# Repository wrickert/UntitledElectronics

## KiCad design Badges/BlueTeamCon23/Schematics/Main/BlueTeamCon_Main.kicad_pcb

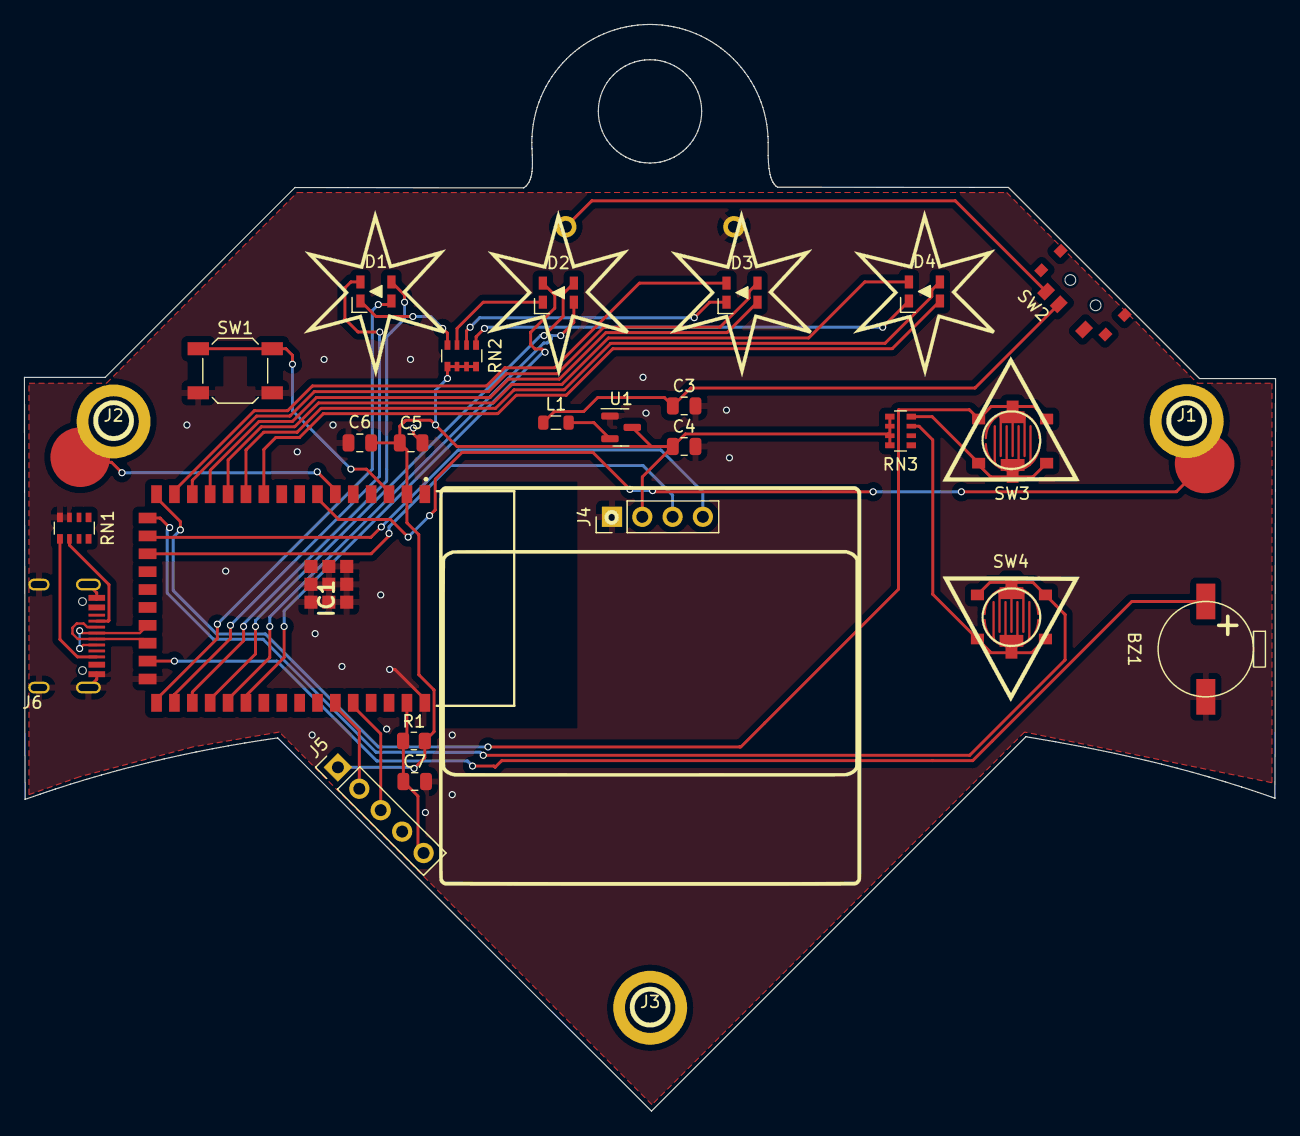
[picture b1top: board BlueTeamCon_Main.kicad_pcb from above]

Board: 2 copper layers, 104.9 x 91.1 mm, 30 parts (1 on the bottom side), 39 nets.

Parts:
BT1: Battery; AA_TH
BZ1: Buzzer; FUET-9032-Buzzer
C3: 10uF; C_0805_2012Metric
C4, C5: 22uF; C_0805_2012Metric
C6, C7: 100nF; C_0805_2012Metric
D1, D2, D3, D4: LED_RGBA; XL-3227RGB_LED
IC1: ESP32-S2-WROOM-I_M22S2H3200US3Q0_; ESP32S2WROOMIM22S2H3200US3Q0
J1, J2, J3: Conn_01x01; Threaded_Standoffs
J4: Display; PinHeader_1x04_P2.54mm_Vertical
J5: Conn_01x05; PinHeader_1x05_P2.54mm_Vertical
J6: USB_C_Plug_USB2.0; USB_C_Receptical-Jing
J7, J8: Cap Sense; CapSense
L1: 10uH; L_0805_2012Metric
R1: 1k; R_0805_2012Metric
RN1: 5.1k; R_Array_Convex_4x0603
RN2, RN3: R_Pack04; R_Array_Convex_4x0603
SW1: Boot; SW_SPST_SKQG_WithoutStem
SW2: SW_SPDT; SK-3296S_switch
SW3: A; BZCN-TSC005A_Button
SW4: B; BZCN-TSC005A_Button
U1: SOT-23

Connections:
+5V: J6.A4 (VBUS), J6.A9 (VBUS), J6.B4 (VBUS), J6.B9 (VBUS)
/D+: IC1.23 (IO20), J6.A6 (D+), J6.B6 (D+)
/D-: IC1.24 (IO21), J6.A7 (D-), J6.B7 (D-)
A_Btn: IC1.16 (IO13), SW3.1
B: IC1.17 (IO14), SW4.1
B1: D1.4 (BK), IC1.27 (IO33)
B2: D2.4 (BK), IC1.31 (IO37)
B3: D3.4 (BK), IC1.13 (IO10)
B4: D4.4 (BK), IC1.10 (IO7)
Boot: IC1.3 (IO0), SW1.1
Buzzer: BZ1.1 (-), IC1.25 (IO26)
G1: D1.2 (GK), IC1.29 (IO35)
G2: D2.2 (GK), IC1.30 (IO36)
G3: D3.2 (GK), IC1.14 (IO11)
G4: D4.2 (GK), IC1.11 (IO8)
unnamed: D1.3 (A), RN2.4 (R4.1)
unnamed: D2.3 (A), RN2.3 (R3.1)
unnamed: D3.3 (A), RN2.2 (R2.1)
unnamed: D4.3 (A), RN2.1 (R1.1)
unnamed: IC1.6 (IO3), J7.1
unnamed: IC1.7 (IO4), J8.1
unnamed: J6.A5 (CC1), RN1.6 (R3.2)
unnamed: J6.B5 (CC2), RN1.5 (R4.2)
unnamed: RN3.3 (R3.1), SW4.2
unnamed: RN3.4 (R4.1), SW3.2
unnamed: L1.2, U1.2 (LX)
PwrTest: C3.1, L1.1, SW2.2 (B)
R1: D1.1 (RK), IC1.28 (IO34)
R2: D2.1 (RK), IC1.32 (IO38)
R3: D3.1 (RK), IC1.15 (IO12)
R4: D4.1 (RK), IC1.12 (IO9)
RX: IC1.38 (RXD0), J5.3
Reset: C7.1, IC1.41 (EN), J5.5, R1.1
SCK: IC1.19 (IO16), J4.3
SDA: IC1.18 (IO15), J4.4
TX: IC1.37 (TXD0), J5.2
VCC: C4.1, C5.1, C6.1, IC1.2 (3V3), J4.2, J5.1, R1.2, RN2.5 (R4.2), RN2.6 (R3.2), RN2.7 (R2.2), RN2.8 (R1.2), RN3.5 (R4.2), RN3.6 (R3.2), RN3.7 (R2.2), RN3.8 (R1.2), U1.3 (VOUT)
VDD: BT1.1 (+), SW2.1 (A)
VSS: BT1.2 (-), BZ1.2 (+), C3.2, C4.2, C5.2, C6.2, C7.2, IC1.1 (GND_1), IC1.26 (GND_2), IC1.42 (GND_3), IC1.43 (GND_4), IC1.44 (GND_5), IC1.45 (GND_6), IC1.46 (GND_7), IC1.47 (GND_8), IC1.48 (GND_9), IC1.49 (GND_10), IC1.50 (GND_11), IC1.51 (GND_12), J4.1, J5.4, J6.A1 (GND), J6.A12 (GND), J6.B1 (GND), J6.B12 (GND), J6.S1 (SHIELD), RN1.3 (R3.1), RN1.4 (R4.1), SW1.2, U1.1 (VSS)

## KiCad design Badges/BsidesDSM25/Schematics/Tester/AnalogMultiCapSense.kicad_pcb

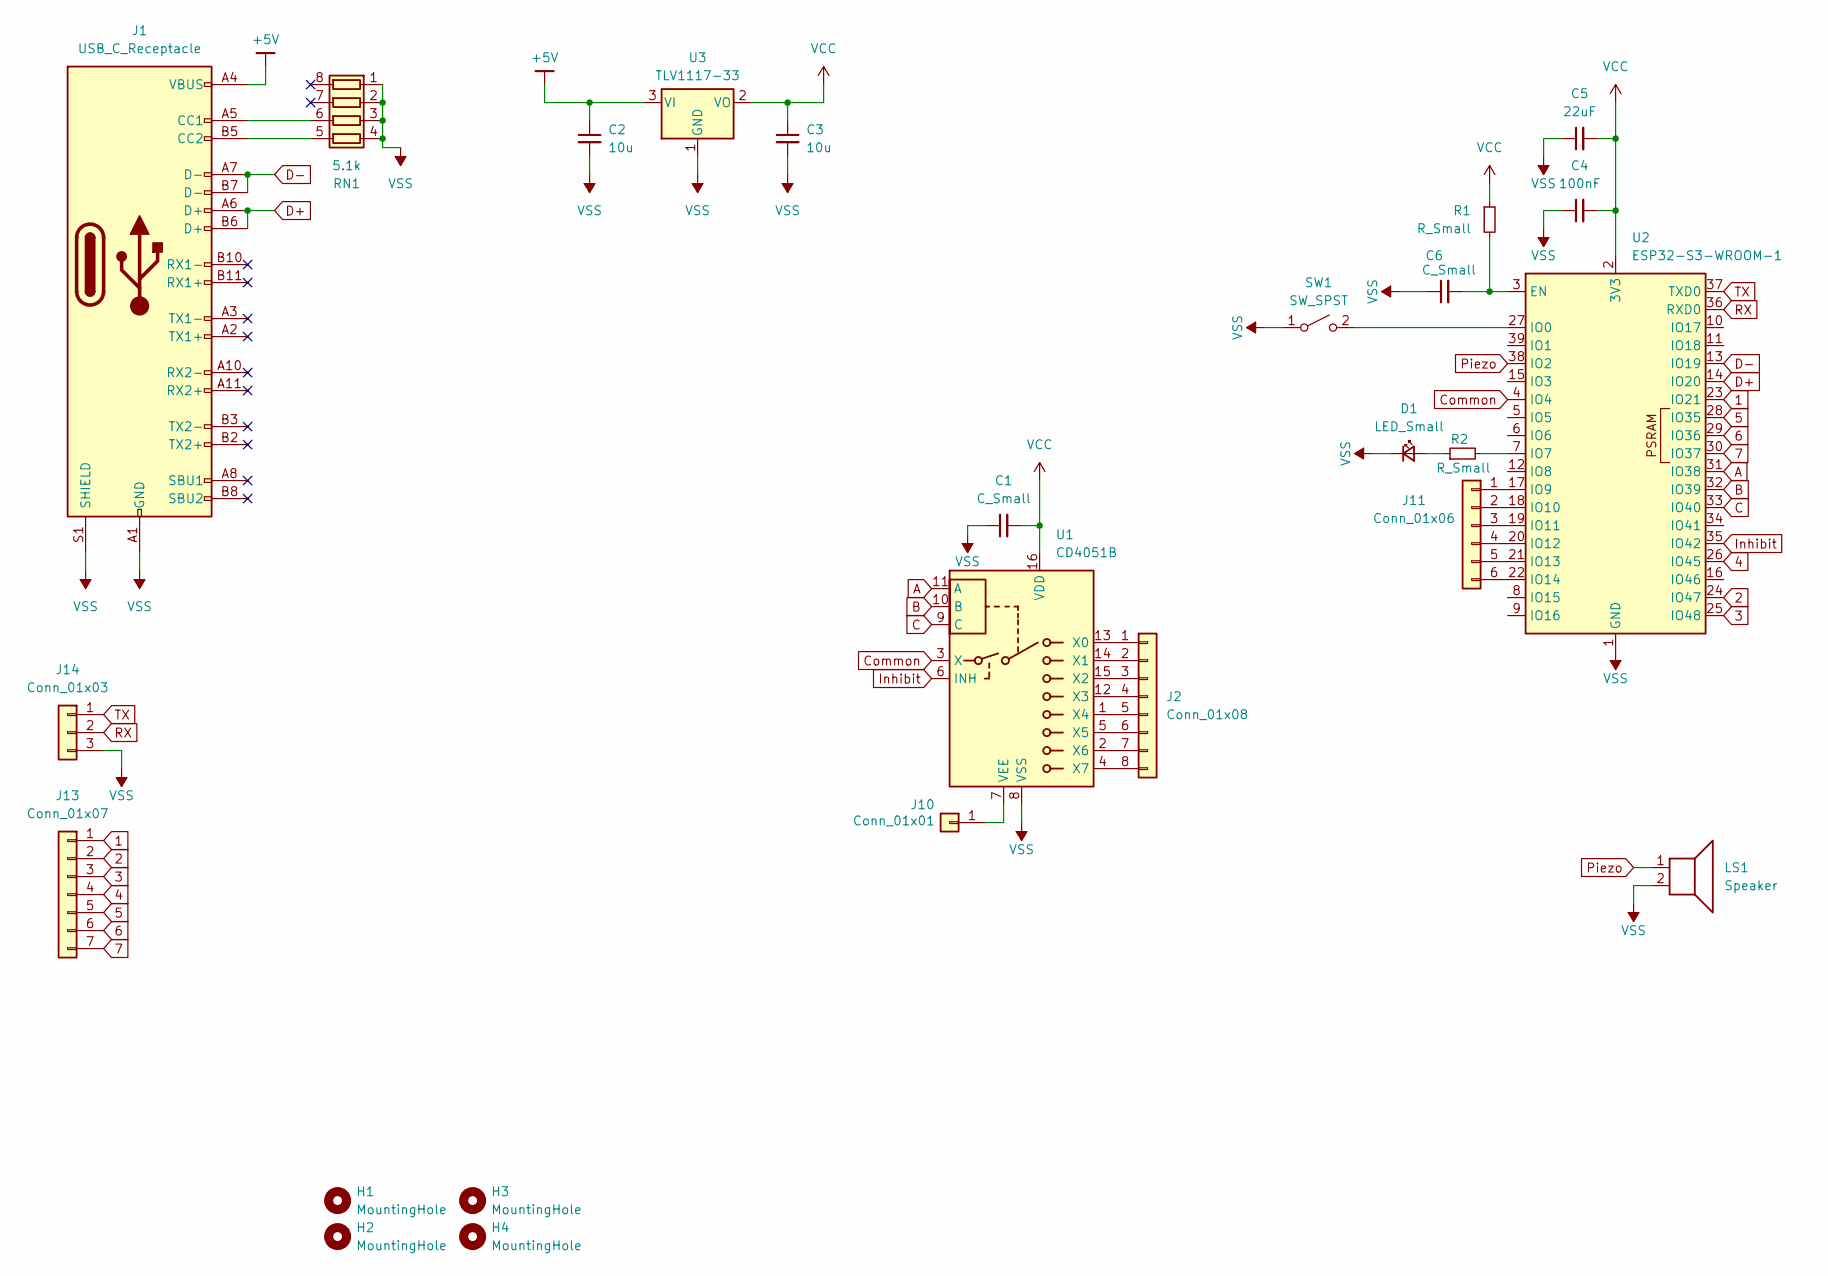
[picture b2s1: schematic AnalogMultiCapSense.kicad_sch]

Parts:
C1, C6: C_Small; C_0805_2012Metric
C2, C3: 10u; C_0805_2012Metric
C4: 100nF; C_0805_2012Metric
C5: 22uF; C_0805_2012Metric
D1: LED_Small; LED_0805_2012Metric
H1, H2, H3, H4: MountingHole; MountingHole_2.2mm_M2
J1: USB_C_Receptacle; USB_C_Receptical-Jing
J2: Conn_01x08; 8CapDemo
J10: Conn_01x01; PinHeader_1x01_P2.54mm_Vertical
J11: Conn_01x06; PinHeader_1x06_P2.54mm_Vertical
J13: Conn_01x07; PinHeader_1x07_P2.54mm_Vertical
J14: Conn_01x03; PinHeader_1x03_P2.54mm_Vertical
LS1: Speaker; Buzzer_Mallory_AST1240MLQ
R1, R2: R_Small; R_0805_2012Metric
RN1: 5.1k; R_Array_Convex_4x0603
SW1: SW_SPST; SW_SPST_Omron_B3FS-100xP
U1: CD4051B; SO-16_3.9x9.9mm_P1.27mm
U2: ESP32-S3-WROOM-1
U3: TLV1117-33; SOT-223-3_TabPin2

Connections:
1: J13.1, U2.23 (IO21)
2: J13.2, U2.24 (IO47)
3: J13.3, U2.25 (IO48)
4: J13.4, U2.26 (IO45)
5: J13.5, U2.28 (IO35)
6: J13.6, U2.29 (IO36)
7: J13.7, U2.30 (IO37)
+5V: C2.1, J1.A4 (VBUS), J1.A9 (VBUS), J1.B4 (VBUS), J1.B9 (VBUS), U3.3 (VI)
A: U1.11 (A), U2.31 (IO38)
B: U1.10 (B), U2.32 (IO39)
C: U1.9 (C), U2.33 (IO40)
Common: U1.3 (X), U2.4 (IO4)
D+: J1.A6 (D+), J1.B6 (D+), U2.14 (IO20)
D-: J1.A7 (D-), J1.B7 (D-), U2.13 (IO19)
Inhibit: U1.6 (INH), U2.35 (IO42)
unnamed: D1.2 (A), R2.1
unnamed: J1.A5 (CC1), RN1.6 (R3.2)
unnamed: J1.B5 (CC2), RN1.5 (R4.2)
unnamed: J2.1, U1.13 (X0)
unnamed: J2.2, U1.14 (X1)
unnamed: J2.3, U1.15 (X2)
unnamed: J2.4, U1.12 (X3)
unnamed: J2.5, U1.1 (X4)
unnamed: J2.6, U1.5 (X5)
unnamed: J2.7, U1.2 (X6)
unnamed: J2.8, U1.4 (X7)
unnamed: J10.1, U1.7 (VEE)
unnamed: J11.1, U2.17 (IO9)
unnamed: J11.2, U2.18 (IO10)
unnamed: J11.3, U2.19 (IO11)
unnamed: J11.4, U2.20 (IO12)
unnamed: J11.5, U2.21 (IO13)
unnamed: J11.6, U2.22 (IO14)
unnamed: SW1.2 (B), U2.27 (IO0)
unnamed: C6.2, R1.2, U2.3 (EN)
unnamed: R2.2, U2.7 (IO7)
Piezo: LS1.1, U2.38 (IO2)
RX: J14.2, U2.36 (RXD0)
TX: J14.1, U2.37 (TXD0)
VCC: C1.2, C3.1, C4.2, C5.2, R1.1, U1.16 (VDD), U2.2 (3V3), U3.2 (VO)
VSS: C1.1, C2.2, C3.2, C4.1, C5.1, C6.1, D1.1 (K), J1.A1 (GND), J1.A12 (GND), J1.B1 (GND), J1.B12 (GND), J1.S1 (SHIELD), J14.3, LS1.2, RN1.1 (R1.1), RN1.2 (R2.1), RN1.3 (R3.1), RN1.4 (R4.1), SW1.1 (A), U1.8 (VSS), U2.1 (GND), U2.40 (GND), U2.41 (GND), U3.1 (GND)

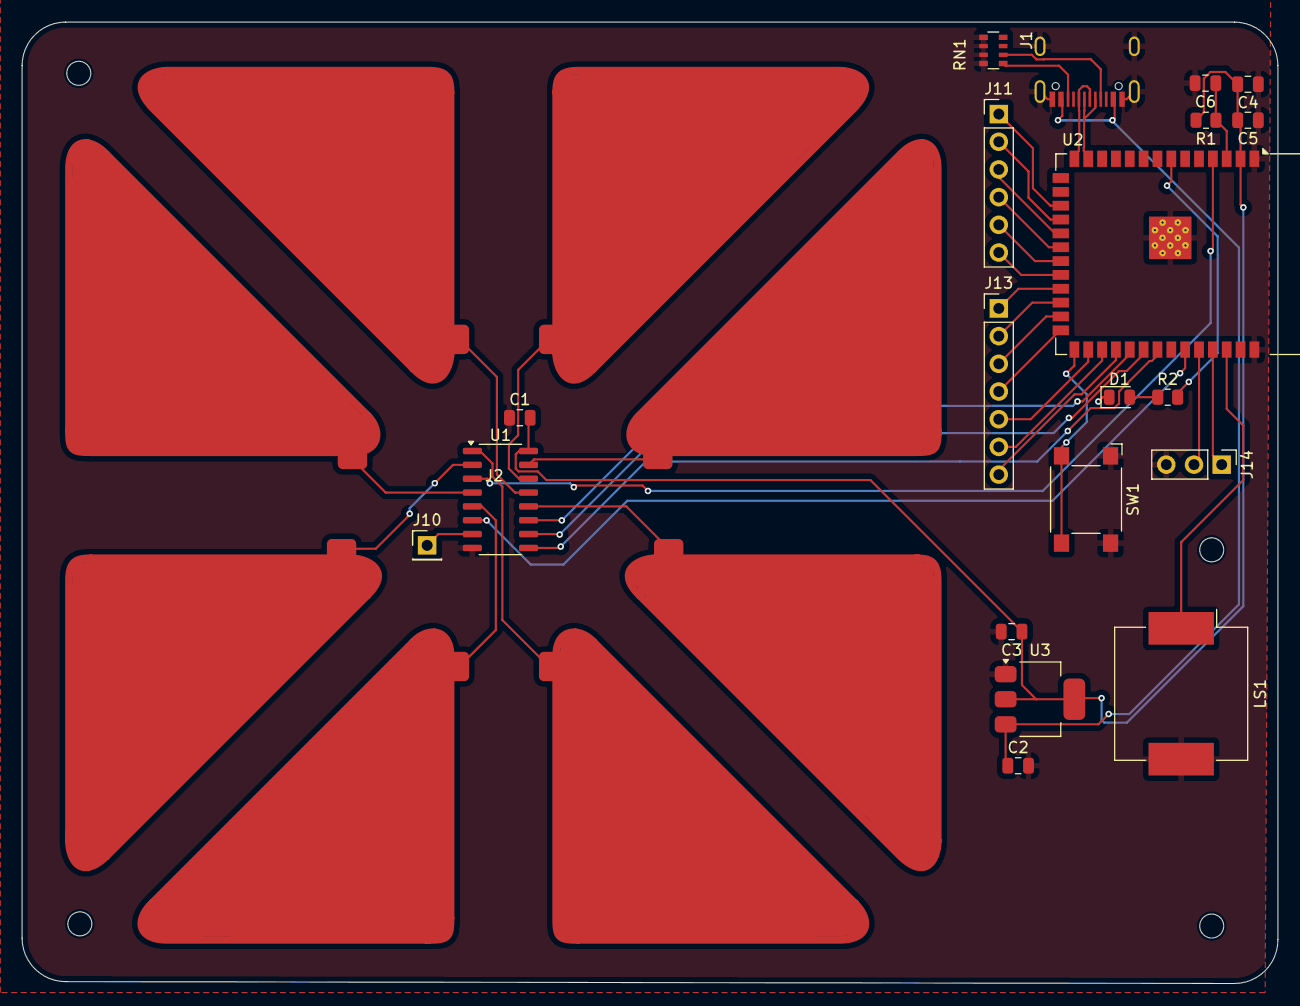
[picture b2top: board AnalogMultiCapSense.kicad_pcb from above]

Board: 2 copper layers, 115.2 x 88.2 mm, 25 parts (0 on the bottom side), 41 nets.

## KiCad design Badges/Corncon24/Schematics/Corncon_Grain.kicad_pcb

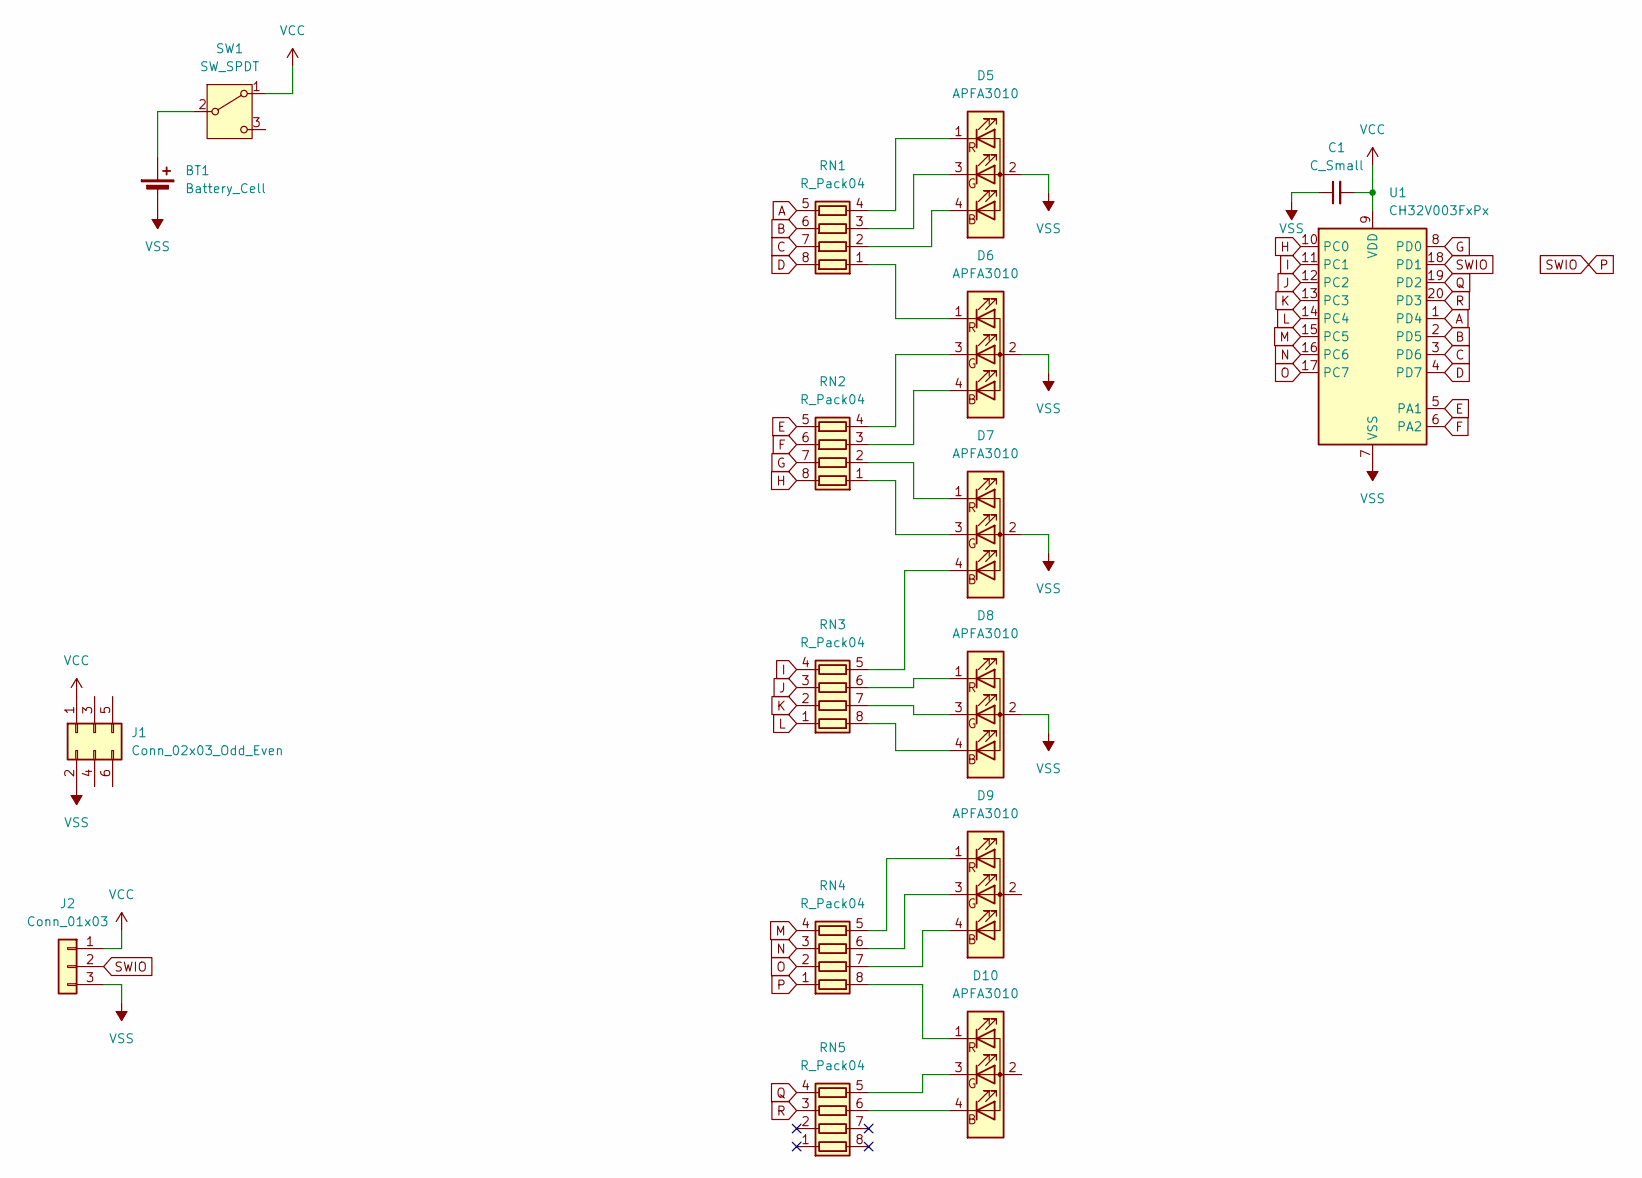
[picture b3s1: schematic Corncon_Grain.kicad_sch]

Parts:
BT1: Battery_Cell; BatteryHolder_Keystone_3008_1x2450
C1: C_Small; C_0805_2012Metric
D5, D6, D7, D8, D9, D10: APFA3010; FM-3510RGBA
J1: Conn_02x03_Odd_Even; PinHeader_2x03_P2.54mm_Vertical
J2: Conn_01x03; PinHeader_1x03_P2.54mm_Vertical
RN1, RN2, RN3, RN4, RN5: R_Pack04; R_Array_Convex_4x0603
SW1: SW_SPDT; SW_SPDT_PCM12
U1: CH32V003FxPx; TSSOP-20_4.4x6.5mm_P0.65mm

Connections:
A: RN1.5 (R4.2), U1.1 (PD4)
B: RN1.6 (R3.2), U1.2 (PD5)
C: RN1.7 (R2.2), U1.3 (PD6)
D: RN1.8 (R1.2), U1.4 (PD7)
E: RN2.5 (R4.2), U1.5 (PA1)
F: RN2.6 (R3.2), U1.6 (PA2)
G: RN2.7 (R2.2), U1.8 (PD0)
H: RN2.8 (R1.2), U1.10 (PC0)
I: RN3.4 (R4.1), U1.11 (PC1)
J: RN3.3 (R3.1), U1.12 (PC2)
K: RN3.2 (R2.1), U1.13 (PC3)
L: RN3.1 (R1.1), U1.14 (PC4)
M: RN4.4 (R4.1), U1.15 (PC5)
N: RN4.3 (R3.1), U1.16 (PC6)
unnamed: BT1.1 (+), SW1.2 (B)
unnamed: D5.4 (B), RN1.2 (R2.1)
unnamed: D5.3 (G), RN1.3 (R3.1)
unnamed: D5.1 (R), RN1.4 (R4.1)
unnamed: D6.4 (B), RN2.3 (R3.1)
unnamed: D6.3 (G), RN2.4 (R4.1)
unnamed: D6.1 (R), RN1.1 (R1.1)
unnamed: D7.4 (B), RN3.5 (R4.2)
unnamed: D7.3 (G), RN2.1 (R1.1)
unnamed: D7.1 (R), RN2.2 (R2.1)
unnamed: D8.4 (B), RN3.8 (R1.2)
unnamed: D8.3 (G), RN3.7 (R2.2)
unnamed: D8.1 (R), RN3.6 (R3.2)
unnamed: D9.4 (B), RN4.7 (R2.2)
unnamed: D9.3 (G), RN4.6 (R3.2)
unnamed: D9.1 (R), RN4.5 (R4.2)
unnamed: D10.4 (B), RN5.6 (R3.2)
unnamed: D10.3 (G), RN5.5 (R4.2)
unnamed: D10.1 (R), RN4.8 (R1.2)
O: RN4.2 (R2.1), U1.17 (PC7)
P: J2.2, RN4.1 (R1.1), U1.18 (PD1)
Q: RN5.4 (R4.1), U1.19 (PD2)
R: RN5.3 (R3.1), U1.20 (PD3)
VCC: C1.2, J1.1, J2.1, SW1.1 (A), U1.9 (VDD)
VSS: BT1.2 (-), C1.1, D5.2 (A), D6.2 (A), D7.2 (A), D8.2 (A), J1.2, J2.3, U1.7 (VSS)

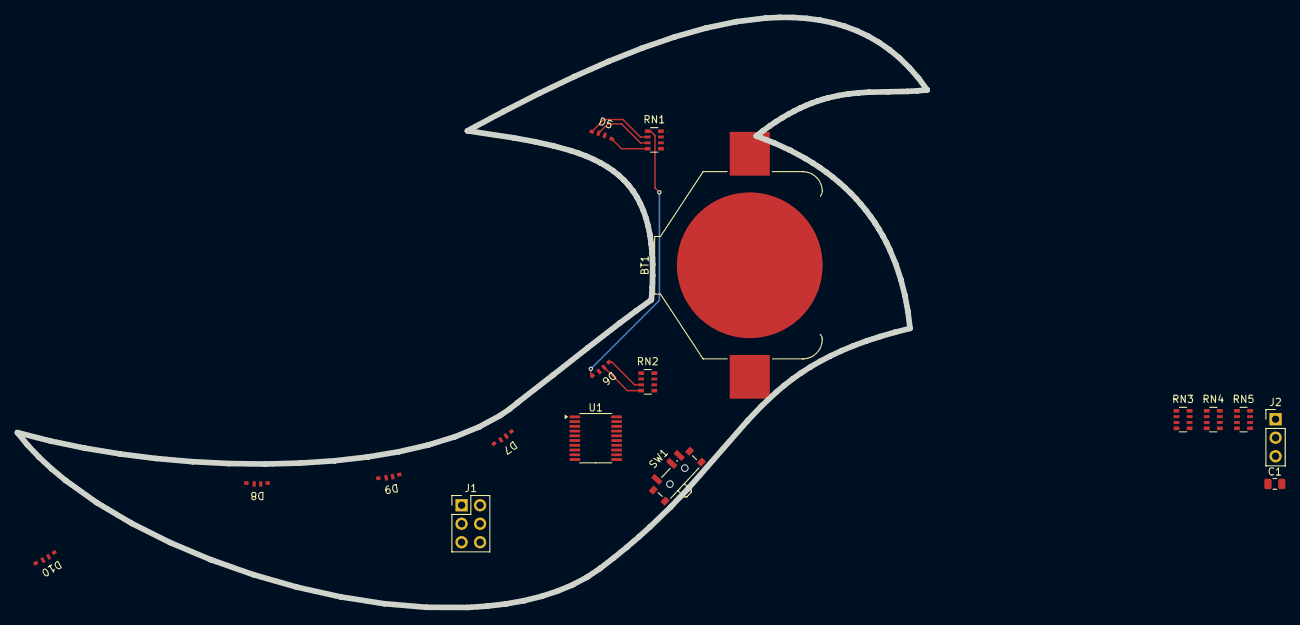
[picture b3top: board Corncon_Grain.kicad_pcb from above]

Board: 2 copper layers, 124.8 x 81.0 mm, 17 parts (0 on the bottom side), 39 nets.

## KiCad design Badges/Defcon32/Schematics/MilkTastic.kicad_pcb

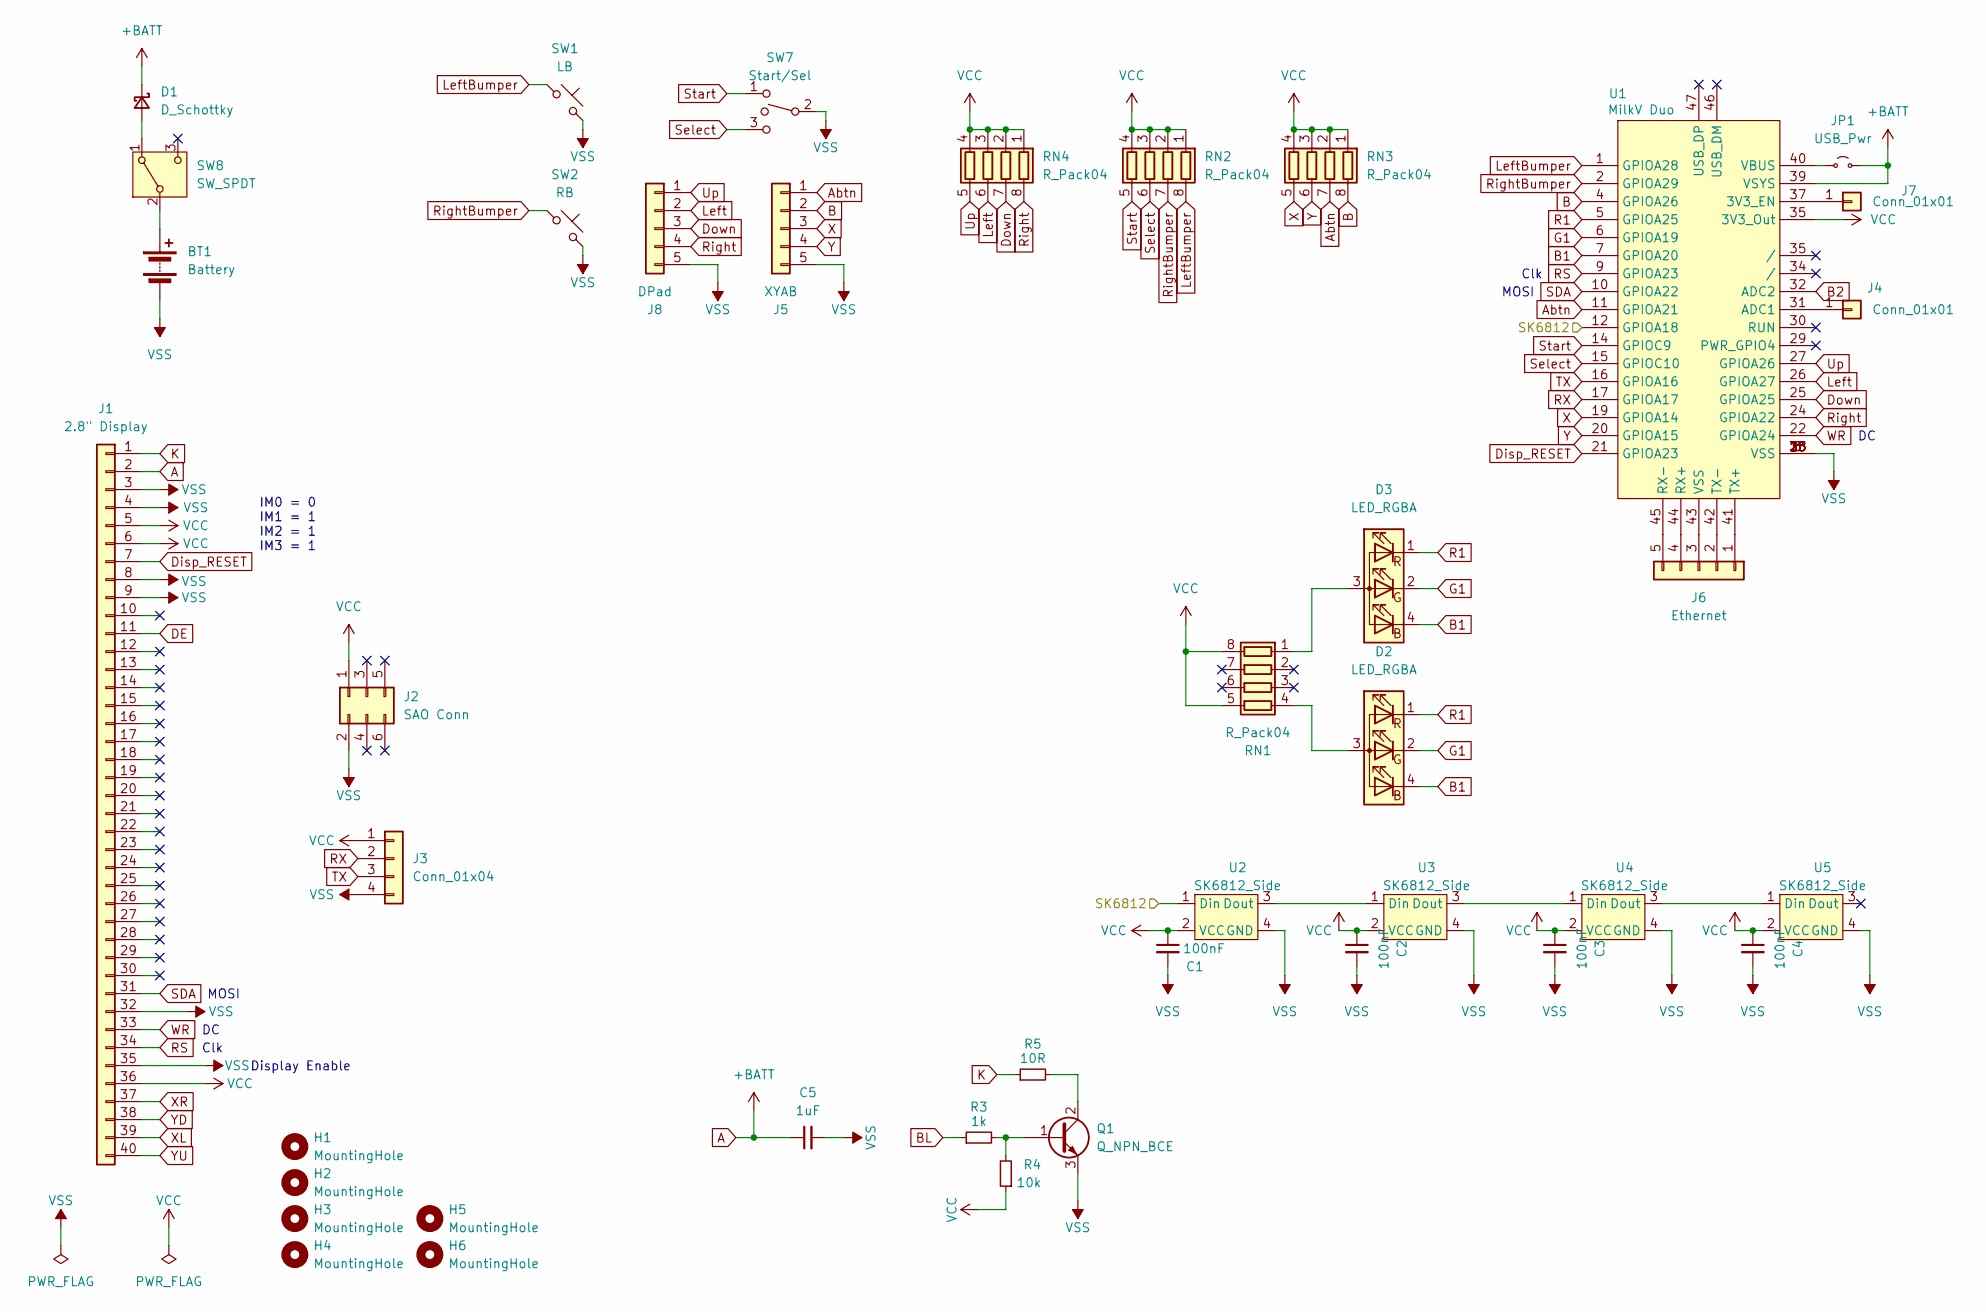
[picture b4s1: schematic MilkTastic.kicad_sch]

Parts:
BT1: Battery; AAA_TH_UM-4
C1, C2, C3, C4: 100nF; C_0805_2012Metric
C5: 1uF; C_0805_2012Metric
D1: D_Schottky; D_0805_2012Metric
D2, D3: LED_RGBA; XL-3227RGB_LED
H1, H2, H3, H4, H5, H6: MountingHole; MountingHole_3.2mm_M3
J1: 2.8" Display; Omron_XF2M-4015-1A_1x40-1MP_P0.5mm_Horizontal
J2: SAO Conn; PinSocket_2x03_P2.54mm_Vertical
J3: Conn_01x04; PinHeader_1x04_P2.54mm_Vertical
J4, J7: Conn_01x01; PinHeader_1x01_P2.54mm_Vertical
J5: XYAB; Xbox_DPad
J6: Ethernet; PinHeader_1x05_P2.54mm_Vertical
J8: DPad; Xbox_DPad
JP1: USB_Pwr; SolderJumper-2_P1.3mm_Open_TrianglePad1.0x1.5mm
Q1: Q_NPN_BCE; SOT-23
R3: 1k; R_0805_2012Metric
R4: 10k; R_0805_2012Metric
R5: 10R; R_0805_2012Metric
RN1, RN2, RN3, RN4: R_Pack04; R_Array_Convex_4x0603
SW1: LB; TSB003A3518A_RightAngle_Anchor
SW2: RB; TSB003A3518A_RightAngle_Anchor
SW7: Start/Sel; StartSel-Dome
SW8: SW_SPDT; SK-3296S_switch
U1: MilkV Duo; MIlkV-Duo
U2, U3, U4, U5: SK6812_Side; SK6812SIDE-A-RVS

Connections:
/SK6812: U1.12 (GPIOA18), U2.1 (Din)
A: C5.1, D1.1 (K), J1.2, JP1.2 (B), U1.39 (VSYS)
Abtn: J5.1, RN3.7 (R2.2), U1.11 (GPIOA21)
B: J5.2, RN3.8 (R1.2), U1.4 (GPIOA26)
B1: D2.4 (BK), D3.4 (BK), U1.7 (GPIOA20)
B2: U1.32 (ADC2)
BL: R3.1
DE: J1.11
Disp_RESET: J1.7, U1.21 (GPIOA23)
Down: J8.3, RN4.7 (R2.2), U1.25 (GPIOA25)
G1: D2.2 (GK), D3.2 (GK), U1.6 (GPIOA19)
K: J1.1, R5.1
Left: J8.2, RN4.6 (R3.2), U1.26 (GPIOA27)
LeftBumper: RN2.8 (R1.2), SW1.1, U1.1 (GPIOA28)
unnamed: BT1.1 (+), SW8.2 (B)
unnamed: D1.2 (A), SW8.1 (A)
unnamed: D2.3 (A), RN1.4 (R4.1)
unnamed: D3.3 (A), RN1.1 (R1.1)
unnamed: J4.1, U1.31 (ADC1)
unnamed: J6.1, U1.41 (TX+)
unnamed: J6.2, U1.42 (TX-)
unnamed: J6.3, U1.43 (VSS)
unnamed: J6.4, U1.44 (RX+)
unnamed: J6.5, U1.45 (RX-)
unnamed: J7.1, U1.37 (3V3_EN)
unnamed: JP1.1 (A), U1.40 (VBUS)
unnamed: Q1.1 (B), R3.2, R4.2
unnamed: Q1.2 (C), R5.2
unnamed: U2.3 (Dout), U3.1 (Din)
unnamed: U3.3 (Dout), U4.1 (Din)
unnamed: U4.3 (Dout), U5.1 (Din)
R1: D2.1 (RK), D3.1 (RK), U1.5 (GPIOA25)
RS: J1.34, U1.9 (GPIOA23)
RX: J3.2, U1.17 (GPIOA17)
Right: J8.4, RN4.8 (R1.2), U1.24 (GPIOA22)
RightBumper: RN2.7 (R2.2), SW2.1, U1.2 (GPIOA29)
SDA: J1.31, U1.10 (GPIOA22)
Select: RN2.6 (R3.2), SW7.3, U1.15 (GPIOC10)
Start: RN2.5 (R4.2), SW7.1, U1.14 (GPIOC9)
TX: J3.3, U1.16 (GPIOA16)
Up: J8.1, RN4.5 (R4.2), U1.27 (GPIOA26)
VCC: C1.1, C2.1, C3.1, C4.1, J1.5, J1.6, J1.36, J2.1, J3.1, R4.1, RN1.5 (R4.2), RN1.8 (R1.2), RN2.1 (R1.1), RN2.2 (R2.1), RN2.3 (R3.1), RN2.4 (R4.1), RN3.1 (R1.1), RN3.2 (R2.1), RN3.3 (R3.1), RN3.4 (R4.1), RN4.1 (R1.1), RN4.2 (R2.1), RN4.3 (R3.1), RN4.4 (R4.1), U1.35 (3V3_Out), U2.2 (VCC), U3.2 (VCC), U4.2 (VCC), U5.2 (VCC)
VSS: BT1.2 (-), C1.2, C2.2, C3.2, C4.2, C5.2, J1.3, J1.4, J1.8, J1.9, J1.32, J1.35, J2.2, J3.4, J5.5, J8.5, Q1.3 (E), SW1.2, SW2.2, SW7.2, U1.3 (VSS), U1.8 (VSS), U1.13 (VSS), U1.18 (VSS), U1.23 (VSS), U1.28 (VSS), U1.33 (VSS), U1.38 (VSS), U2.4 (GND), U3.4 (GND), U4.4 (GND), U5.4 (GND)
WR: J1.33, U1.22 (GPIOA24)
X: J5.3, RN3.5 (R4.2), U1.19 (GPIOA14)
XL: J1.39
XR: J1.37
Y: J5.4, RN3.6 (R3.2), U1.20 (GPIOA15)
YD: J1.38
YU: J1.40

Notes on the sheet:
Clk
Display Enable
MOSI
IM0 = 0 IM1 = 1 IM2 = 1 IM3 = 1

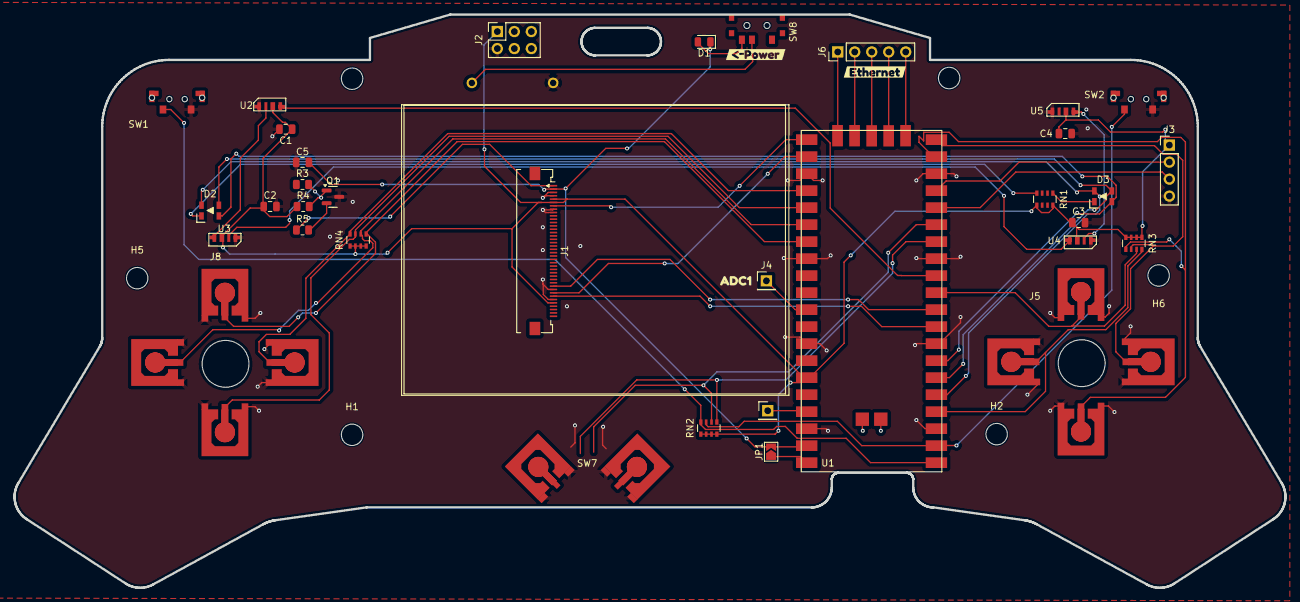
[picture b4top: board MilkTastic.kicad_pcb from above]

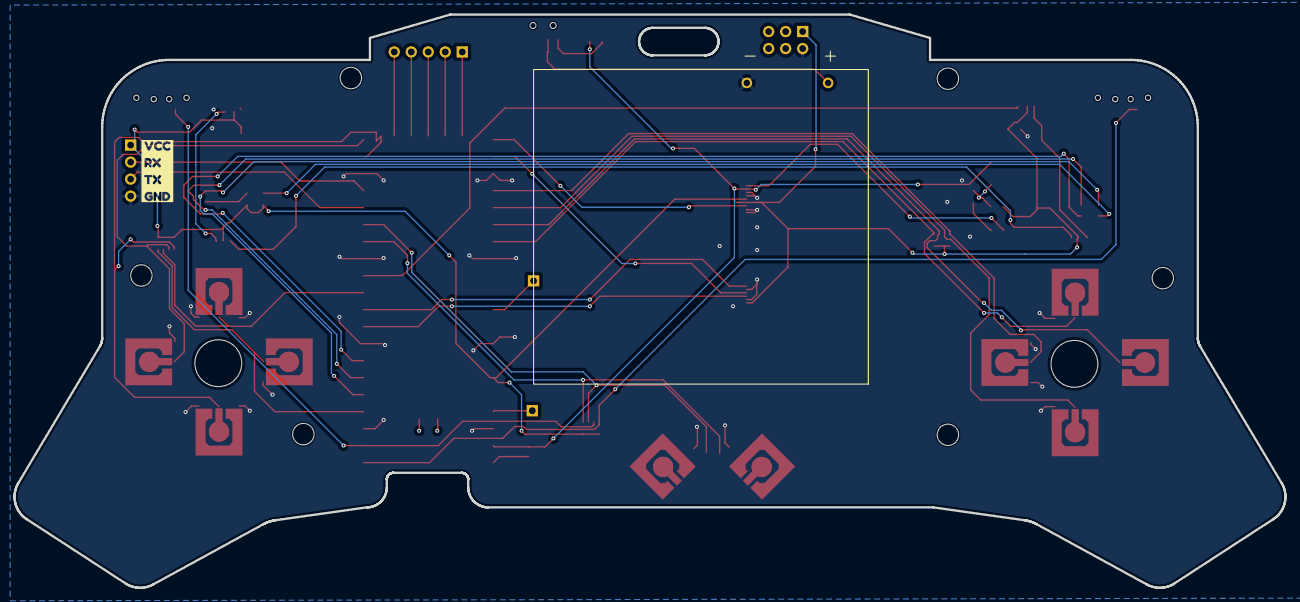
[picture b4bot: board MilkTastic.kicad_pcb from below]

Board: 2 copper layers, 189.9 x 85.6 mm, 45 parts (2 on the bottom side), 43 nets.

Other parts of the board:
kibuzzard-6692EF0B: G***; kibuzzard-6692EF0B
kibuzzard-6692EF2E: G***; kibuzzard-6692EF2E
kibuzzard-6692EF4B: G***; kibuzzard-6692EF4B
kibuzzard-6692EF58: G***; kibuzzard-6692EF58

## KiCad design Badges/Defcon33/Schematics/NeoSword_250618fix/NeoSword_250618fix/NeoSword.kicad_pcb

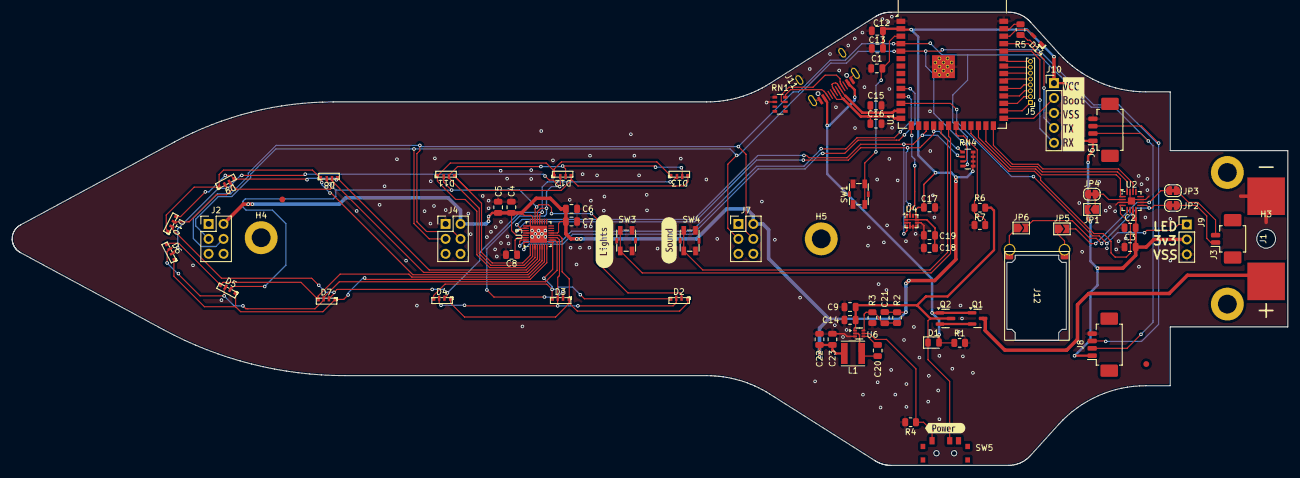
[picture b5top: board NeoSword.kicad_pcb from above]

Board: 2 copper layers, 217.0 x 77.1 mm, 83 parts (0 on the bottom side), 67 nets.

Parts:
C1, C3, C4, C7, C13, C17, C19, C20: 100nF; C_0805_2012Metric
C2, C6, C9, C14: 10uF; C_0805_2012Metric
C5, C8, C18: 1uF; C_0805_2012Metric
C12, C22, C23: 22uF; C_0805_2012Metric
C15, C16: 20pF; C_0805_2012Metric
C21: 47pF; C_0805_2012Metric
D1: D_Schottky; D_0805_2012Metric
D2, D3, D4, D5, D6, D7, D8, D9, D10, D11, D12, D13: APFA3010; FM-3510RGBA-SG_RGB
D14: RED; MHS171CRCT_side_led
H1, H2, H4, H5: MountingHole; MountingHole_3.2mm_M3_DIN965_Pad
H3: MountingHole; MountingHole_3.2mm_M3
J1: AA Batteries; 1016_2AA
J2, J4, J7: Conn_02x03_Odd_Even; PinHeader_2x03_P2.54mm_Vertical
J3: Speaker; Molex_PicoBlade_53261-0271_1x02-1MP_P1.25mm_Horizontal
J5: Conn_01x08; PinHeader_1x08_P1.00mm_Vertical
J6, J8: Conn_01x04; Molex_PicoBlade_53261-0471_1x04-1MP_P1.25mm_Horizontal
J9: Conn_01x03; PinHeader_1x03_P2.54mm_Vertical
J10: Prog; PinHeader_1x05_P2.54mm_Vertical
J11: USB_C_Plug_USB2.0; USB_C_Receptical-Jing
J12: Speaker; CMS-151103-088SP_speaker
JP1: Jumper Open; SolderJumper-2_P1.3mm_Open_TrianglePad1.0x1.5mm
JP2, JP3, JP4: Jumper Bridged; SolderJumper-2_P1.3mm_Bridged_RoundedPad1.0x1.5mm
JP5, JP6: Jumper_2_Small_Open; SolderJumper-2_P1.3mm_Open_TrianglePad1.0x1.5mm
L1: 2.2uH; L_Vishay_IFSC-1515AH_4x4x1.8mm
Q1, Q2: PMOS; SOT-23
R1, R2, R4: 100k; R_0805_2012Metric
R3, R6, R7: 22k; R_0805_2012Metric
R5: 150; R_0805_2012Metric
RN1, RN4: 5.1k; R_Array_Convex_4x0603
SW1: SW_SPST; TS3315A
SW3: Lights; TS3315A
SW4: Sound; TS3315A
SW5: SW_SPDT; SK-3296S_switch
U1: ESP32-S3-WROOM-1
U2: MAX98357A; TQFN-16-1EP_3x3mm_P0.5mm_EP1.23x1.23mm
U3: AW20072QNR; QFN-32-1EP_4x4mm_P0.4mm_EP2.9x2.9mm
U4: LIS2HH12; LGA-12_2x2mm_P0.5mm
U6: TPS562243; SOT-563
kibuzzard-684F57A2: G***; kibuzzard-684F57A2
kibuzzard-684F57B2: G***; kibuzzard-684F57B2
kibuzzard-684F5906: G***; kibuzzard-684F5906
kibuzzard-6850B9A9: G***; kibuzzard-6850B9A9

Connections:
3v3: C2.2, C3.2, C4.1, C5.1, C6.1, C7.1, C12.2, C13.2, C17.1, C18.2, C19.2, C21.1, C22.1, C23.1, J2.2, J4.2, J6.1, J7.2, J8.1, J9.2, J10.1, JP1.2 (B), L1.2, R2.1, RN4.5 (R4.2), RN4.6 (R3.2), RN4.7 (R2.2), RN4.8 (R1.2), U1.2 (3V3), U2.7 (VDD), U2.8 (VDD), U3.13 (VBAT), U3.23 (VBAT), U3.29 (VCC), U4.2 (~CS), U4.9 (Vdd), U4.10 (Vdd_IO)
+5V: D1.2 (A), J11.A4 (VBUS), J11.A9 (VBUS), J11.B4 (VBUS), J11.B9 (VBUS), Q1.1 (G), Q2.1 (G), R1.1
/D+: C16.1, J11.A6 (D+), J11.B6 (D+), U1.14 (USB_D+)
/D-: C15.1, J11.A7 (D-), J11.B7 (D-), U1.13 (USB_D-)
ACT: U1.15 (IO3), U4.12 (INT1)
BattPos: J1.1, Q1.3 (D)
BitClk: U1.25 (IO48), U2.16 (BCLK)
Boot: J10.2, U1.27 (IO0)
BuckEn: R4.1, SW5.3 (C), U6.5 (EN)
C1: D2.2 (A), D5.2 (A), D8.2 (A), D11.2 (A), U3.22 (C1)
C2: D3.2 (A), D6.2 (A), D9.2 (A), D12.2 (A), U3.21 (C2)
C3: D4.2 (A), D7.2 (A), D10.2 (A), D13.2 (A), U3.20 (C3)
Din: U1.24 (IO47), U2.1 (DIN)
LEDen: U1.10 (IO17), U3.32 (EN)
LEDint: U1.11 (IO18), U3.31 (INITN)
LEDout: J9.1, U1.12 (IO8)
LRClk: U1.26 (IO45), U2.14 (LRCLK)
Lights: SW3.1 (A), U1.20 (IO12)
unnamed: D14.2 (A), R5.2
unnamed: D14.1 (K), U1.38 (IO2)
unnamed: J3.1, JP2.2 (B)
unnamed: J3.2, JP3.2 (B)
unnamed: J5.1, U1.28 (IO35)
unnamed: J5.2, U1.29 (IO36)
unnamed: J5.3, U1.30 (IO37)
unnamed: J5.4, U1.31 (IO38)
unnamed: J5.5, U1.32 (IO39)
unnamed: J5.6, U1.33 (IO40)
unnamed: J5.7, U1.34 (IO41)
unnamed: J5.8, U1.35 (IO42)
unnamed: J11.A5 (CC1), RN1.7 (R2.2)
unnamed: J11.B5 (CC2), RN1.8 (R1.2)
unnamed: J12.1, JP5.1 (A)
unnamed: J12.2, JP6.1 (A)
unnamed: JP1.1 (A), JP4.2 (B), U2.2 (GAIN_SLOT)
unnamed: JP2.1 (A), JP6.2 (B), U2.9 (OUTP)
unnamed: JP3.1 (A), JP5.2 (B), U2.10 (OUTN)
unnamed: Q1.2 (S), Q2.2 (S)
unnamed: C1.2, SW1.2 (B), U1.3 (EN)
unnamed: R5.1, U1.39 (IO1)
unnamed: R6.1, R7.2, U1.21 (IO13)
unnamed: C8.2, U3.30 (CBP)
unnamed: C20.2, L1.1, U6.2 (SW)
unnamed: C20.1, U6.4 (VBST)
unnamed: C21.2, R2.2, R3.1, U6.6 (VFB)
R1: D11.4 (B), D12.4 (B), D13.4 (B), U3.1 (R1)
R2: D11.3 (G), D12.3 (G), D13.3 (G), U3.2 (R2)
R3: D11.1 (R), D12.1 (R), D13.1 (R), U3.3 (R3)
R4: D8.4 (B), D9.4 (B), D10.4 (B), U3.4 (R4)
R5: D8.3 (G), D9.3 (G), D10.3 (G), U3.5 (R5)
R6: D8.1 (R), D9.1 (R), D10.1 (R), U3.6 (R6)
R7: D5.4 (B), D6.4 (B), D7.4 (B), U3.7 (R7)
R8: D5.1 (R), D6.1 (R), D7.1 (R), U3.8 (R8)
R9: D2.4 (B), D3.4 (B), D4.4 (B), U3.9 (R9)
R10: D5.3 (G), D6.3 (G), D7.3 (G), U3.10 (R10)
R11: D2.3 (G), D3.3 (G), D4.3 (G), U3.11 (R11)
R12: D2.1 (R), D3.1 (R), D4.1 (R), U3.12 (R12)
RX: J10.5, U1.36 (RXD0)
SCL: RN4.1 (R1.1), U1.18 (IO10), U3.27 (SCL), U4.1 (SCL/SPC)
SCL2: J2.3, J4.3, J6.3, J7.3, J8.3, RN4.3 (R3.1), U1.5 (IO5)
SD: U1.23 (IO21), U2.4 (~SD_MODE)
SDA: RN4.2 (R2.1), U1.17 (IO9), U3.26 (SDA), U4.4 (SDA/SDI)
SDA2: J2.4, J4.4, J6.2, J7.4, J8.2, RN4.4 (R4.1), U1.4 (IO4)
Sound: SW4.1 (A), U1.19 (IO11)
TX: J10.4, U1.37 (TXD0)
VSS: C1.1, C2.1, C3.1, C4.2, C5.2, C6.2, C7.2, C8.1, C9.2, C12.1, C13.1, C14.2, C15.2, C16.2, C17.2, C18.1, C19.1, C22.2, C23.2, J1.2, J2.1, J4.1, J6.4, J7.1, J8.4, J9.3, J10.3, J11.A1 (GND), J11.A12 (GND), J11.B1 (GND), J11.B12 (GND), J11.S1 (SHIELD), JP4.1 (A), R1.2, R3.2, R4.2, R7.1, RN1.1 (R1.1), RN1.2 (R2.1), SW1.1 (A), SW3.2 (B), SW4.2 (B), U1.1 (GND), U1.40 (GND), U1.41 (GND), U2.3 (GND), U2.11 (GND), U2.15 (GND), U2.17 (PAD), U3.24 (CLKIO), U3.25 (AD), U3.28 (VSS), U3.33 (VSS), U4.3 (SA0/SDO), U4.5 (RES), U4.6 (GND), U4.7 (GND), U4.8 (GND), U6.3 (GND)
vBat: C9.1, C14.1, D1.1 (K), Q2.3 (D), R6.2, SW5.2 (B), U6.1 (VIN)
